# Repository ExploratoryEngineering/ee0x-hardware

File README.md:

# ee0x-hardware

* EE Eagle Library contains Eagle packages for ee0x modules and components used in the boards in this repository.
* EE02 v.1 Breakout is a breakout board for the initial version of EE02. This is an early version of the module that has a larger footprint than the production version.
* EE02 CO2 Sensor is an experimental gas sensor board for the initial version of EE02.

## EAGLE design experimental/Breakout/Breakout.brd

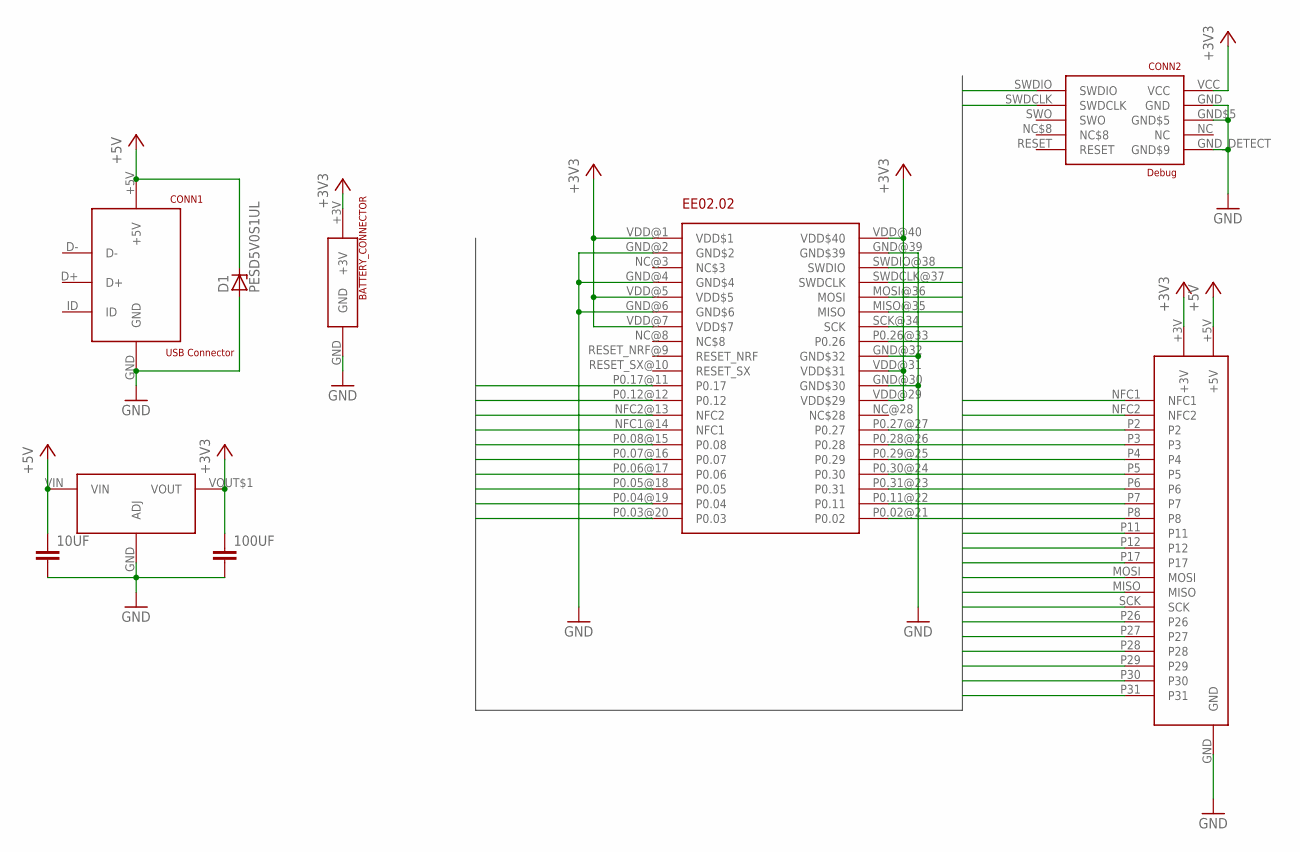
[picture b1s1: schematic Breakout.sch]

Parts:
10UF, 100UF: 4.7UF-0805; 0805
BATTERY_CONNECTOR: 3V_BATTERY_CONNECTOR
CONN1: USB Connector; USB_MICRO_B
CONN2: Debug; NRF52-P19-CONNECTOR
D1: PESD5V0S1UL; SOD882
EE02.02: EE02_02
U$4: LM1117; SOT-223
U$5: EE02_SHIELD_HEADERSHIELD; EE02_SHIELD_HEADER

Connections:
+3V3: 100UF.1, BATTERY_CONNECTOR.+3V, CONN2.VCC, EE02.02.VDD@1 (VDD$1), EE02.02.VDD@5 (VDD$5), EE02.02.VDD@7 (VDD$7), EE02.02.VDD@29 (VDD$29), EE02.02.VDD@31 (VDD$31), EE02.02.VDD@40 (VDD$40), U$4.VOUT$1 (VOUT), U$5.+3V
+5V: 10UF.1, CONN1.+5V, D1.CATHODE (C), U$4.VIN, U$5.+5V
GND: 10UF.2, 100UF.2, BATTERY_CONNECTOR.GND, CONN1.GND, CONN2.GND, CONN2.GND$5, CONN2.GND_DETECT (GND$9), D1.ANODE (A), EE02.02.GND@2 (GND$2), EE02.02.GND@4 (GND$4), EE02.02.GND@6 (GND$6), EE02.02.GND@30 (GND$30), EE02.02.GND@32 (GND$32), EE02.02.GND@39 (GND$39), U$4.GND (ADJ), U$5.GND
MISO: EE02.02.MISO@35 (MISO), U$5.MISO
MOSI: EE02.02.MOSI@36 (MOSI), U$5.MOSI
NFC1: EE02.02.NFC1@14 (NFC1), U$5.NFC1
NFC2: EE02.02.NFC2@13 (NFC2), U$5.NFC2
P2: EE02.02.P0.02@21 (P0.02), U$5.P2
P3: EE02.02.P0.03@20 (P0.03), U$5.P3
P4: EE02.02.P0.04@19 (P0.04), U$5.P4
P5: EE02.02.P0.05@18 (P0.05), U$5.P5
P6: EE02.02.P0.06@17 (P0.06), U$5.P6
P7: EE02.02.P0.07@16 (P0.07), U$5.P7
P8: EE02.02.P0.08@15 (P0.08), U$5.P8
P11: EE02.02.P0.11@22 (P0.11), U$5.P11
P12: EE02.02.P0.12@12 (P0.12), U$5.P12
P17: EE02.02.P0.17@11 (P0.17), U$5.P17
P26: EE02.02.P0.26@33 (P0.26), U$5.P26
P27: EE02.02.P0.27@27 (P0.27), U$5.P27
P28: EE02.02.P0.28@26 (P0.28), U$5.P28
P29: EE02.02.P0.29@25 (P0.29), U$5.P29
P30: EE02.02.P0.30@24 (P0.30), U$5.P30
P31: EE02.02.P0.31@23 (P0.31), U$5.P31
SCK: EE02.02.SCK@34 (SCK), U$5.SCK
SWDCLK: CONN2.SWDCLK, EE02.02.SWDCLK@37 (SWDCLK)
SWDIO: CONN2.SWDIO, EE02.02.SWDIO@38 (SWDIO)

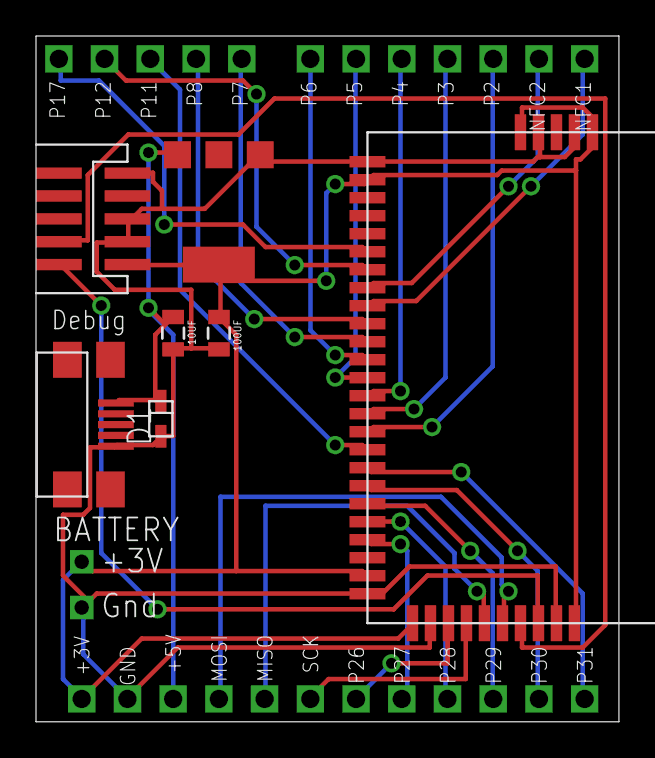
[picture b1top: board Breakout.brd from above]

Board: 2 copper layers, 32.4 x 38.1 mm, 9 parts (0 on the bottom side), 26 nets.

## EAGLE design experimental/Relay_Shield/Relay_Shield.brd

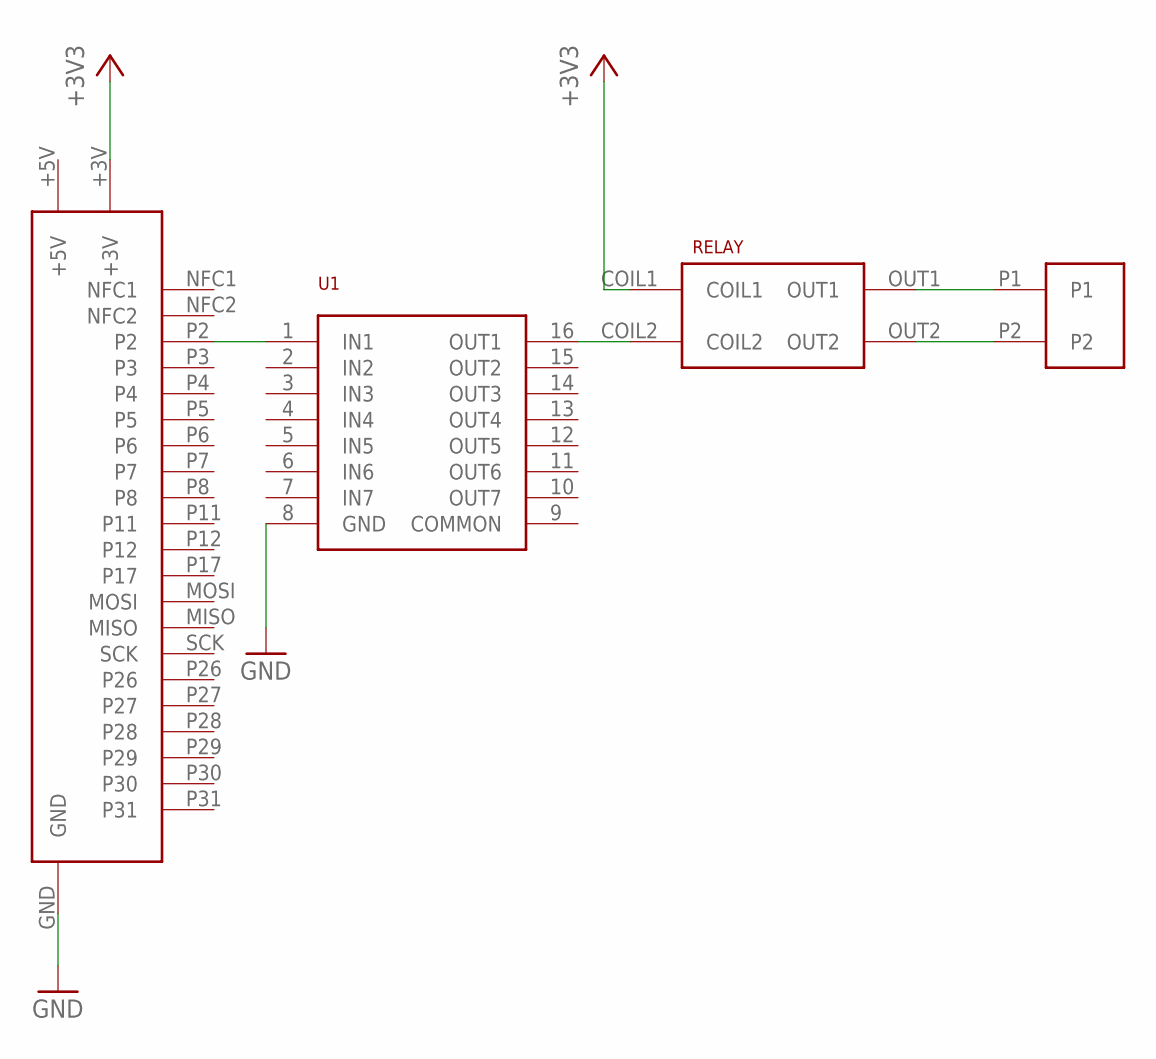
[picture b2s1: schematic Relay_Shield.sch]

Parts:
RELAY: 3V_RELAY_OZ-SS-103LM1
U1: ULN2003D1013TR; SO16-NARROW
U$1: EE02_SHIELD_HEADERSHIELD; EE02_SHIELD_HEADER
U$2: LOAD_TERMINAL_2P; LOAD_CONNECTOR_2P

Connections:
+3V3: RELAY.COIL1, U$1.+3V
GND: U1.8 (GND), U$1.GND
unnamed: U1.1 (IN1), U$1.P2
unnamed: RELAY.COIL2, U1.16 (OUT1)
unnamed: RELAY.OUT1, U$2.P1
unnamed: RELAY.OUT2, U$2.P2

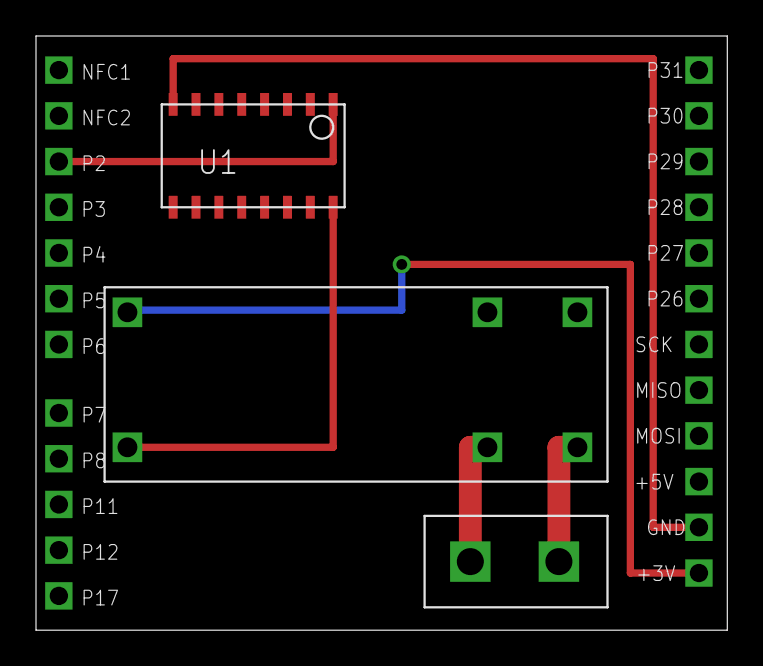
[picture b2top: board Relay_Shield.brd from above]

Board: 2 copper layers, 38.4 x 33.0 mm, 4 parts (0 on the bottom side), 6 nets.

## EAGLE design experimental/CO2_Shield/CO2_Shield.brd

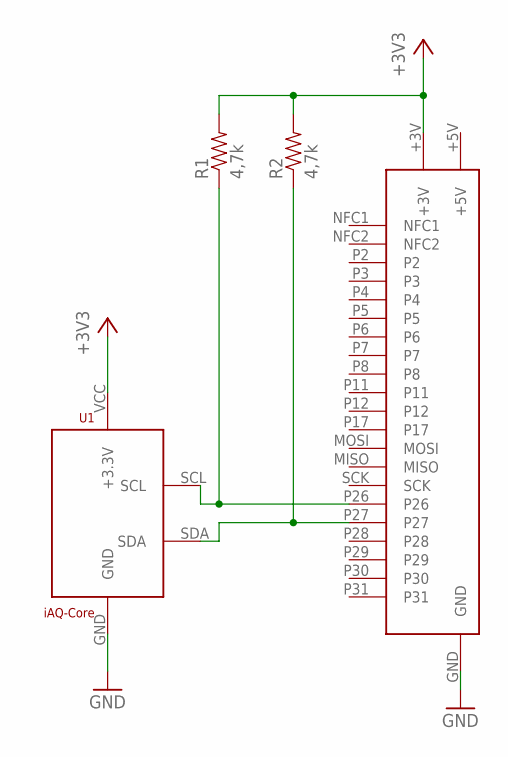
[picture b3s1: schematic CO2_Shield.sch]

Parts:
R1, R2: 4,7k; 0805
U1: iAQ-Core; IAQ-CORE
U$1: EE02_SHIELD_HEADERSHIELD; EE02_SHIELD_HEADER

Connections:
+3V3: R1.2, R2.2, U1.VCC (+3.3V), U$1.+3V
GND: U1.GND, U$1.GND
unnamed: R2.1, U1.SDA, U$1.P27
unnamed: R1.1, U1.SCL, U$1.P26

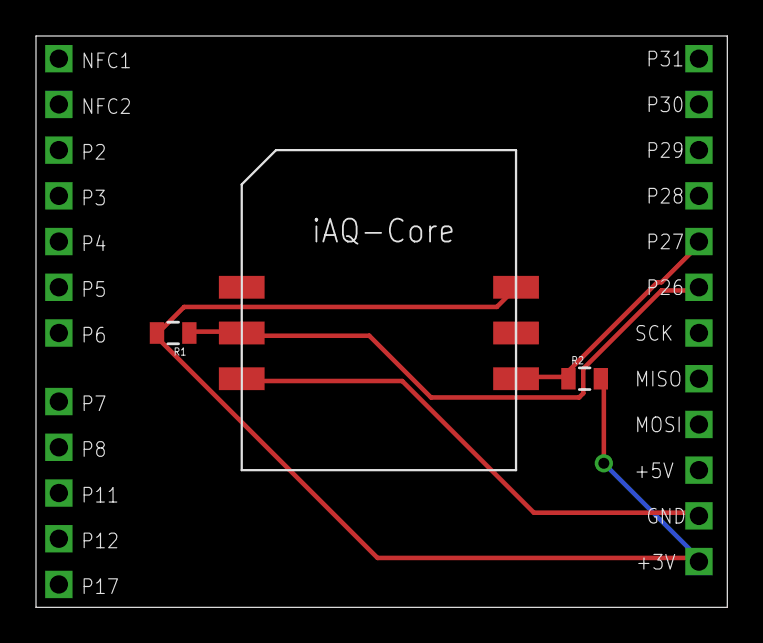
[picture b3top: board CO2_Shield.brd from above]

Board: 2 copper layers, 38.4 x 31.7 mm, 4 parts (0 on the bottom side), 4 nets.

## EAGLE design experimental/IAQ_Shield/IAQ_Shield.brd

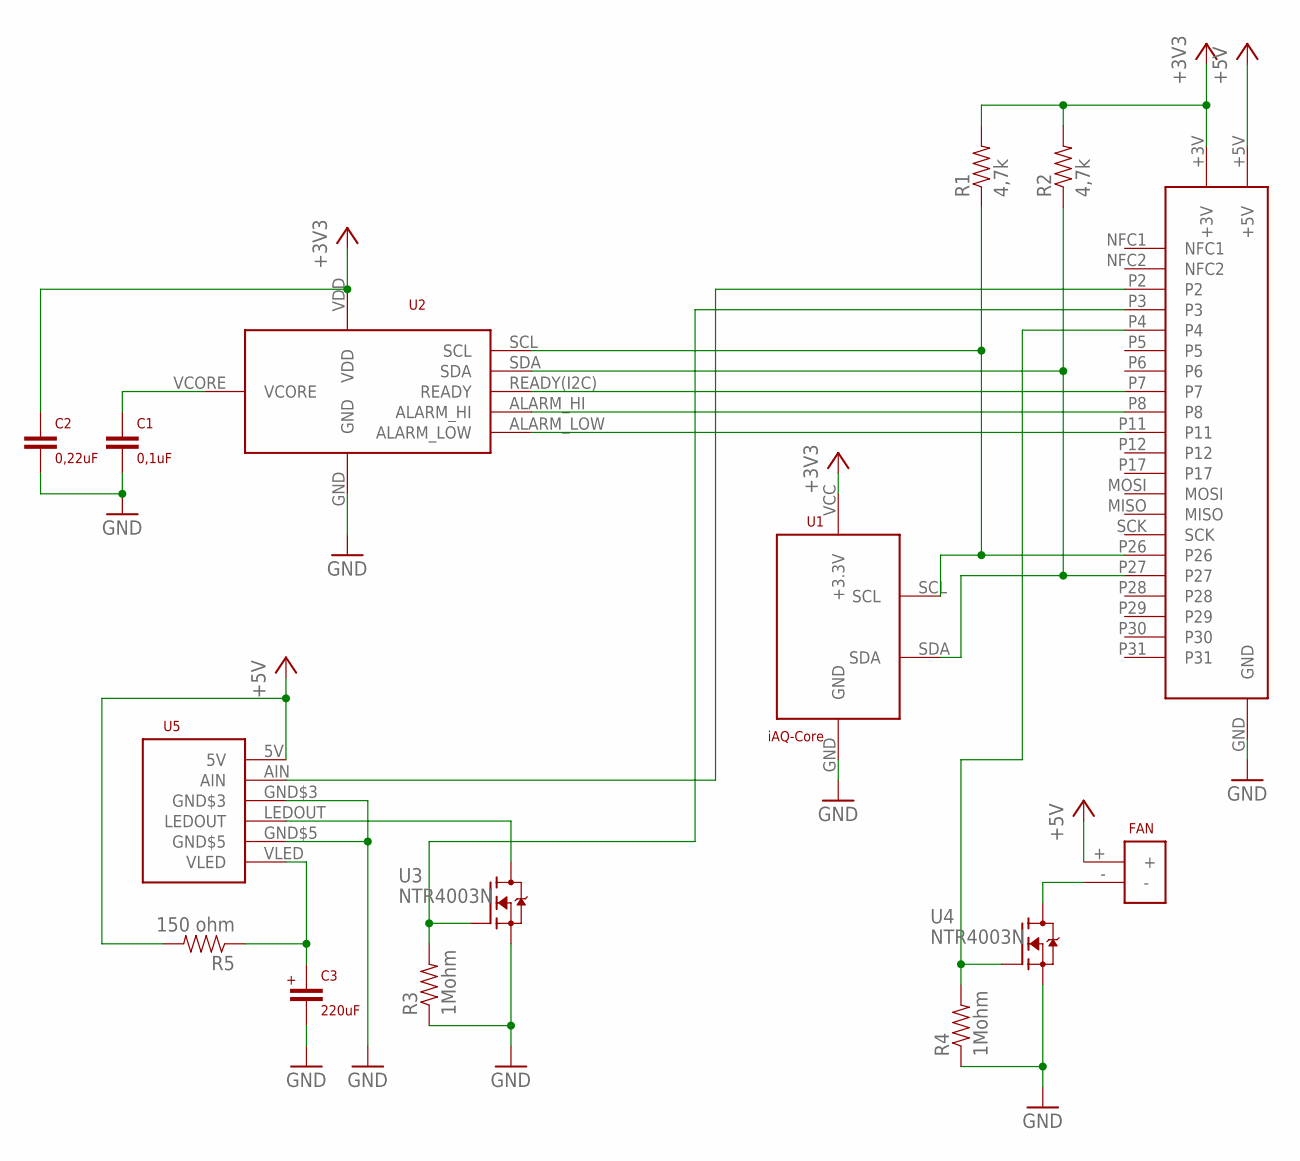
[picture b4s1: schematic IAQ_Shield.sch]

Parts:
C1: 0,1uF; 0805
C2: 0,22uF; 0805
C3: 220uF; UWT1C221MCL1GS_ALUMINIUM
FAN: POWER_SOLDER_PADS_2P
R1, R2: 4,7k; 0805
R3, R4: 1Mohm; 0805
R5: 150 ohm; 0805
U1: iAQ-Core; IAQ-CORE
U2: CHIPCAP2
U3, U4: NTR4003N; SOT23
U5: DN7C3CA006
U$1: EE02_SHIELD_HEADERSHIELD; EE02_SHIELD_HEADER

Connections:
+3V3: C2.1, R1.2, R2.2, U1.VCC (+3.3V), U2.VDD, U$1.+3V
+5V: FAN.+, R5.2, U5.5V, U$1.+5V
GND: C1.2, C2.2, C3.-, R3.1, R4.1, U1.GND, U2.GND, U3.2 (S), U4.2 (S), U5.GND$3, U5.GND$5, U$1.GND
unnamed: R2.1, U1.SDA, U2.SDA, U$1.P27
unnamed: R1.1, U1.SCL, U2.SCL, U$1.P26
unnamed: U5.AIN, U$1.P2
unnamed: U3.3 (D), U5.LEDOUT
unnamed: U2.READY(I2C) (READY), U$1.P7
unnamed: C1.1, U2.VCORE
unnamed: U2.ALARM_HI, U$1.P8
unnamed: U2.ALARM_LOW, U$1.P11
unnamed: R3.2, U3.1 (G), U$1.P3
unnamed: C3.+, R5.1, U5.VLED
unnamed: R4.2, U4.1 (G), U$1.P4
unnamed: FAN.-, U4.3 (D)

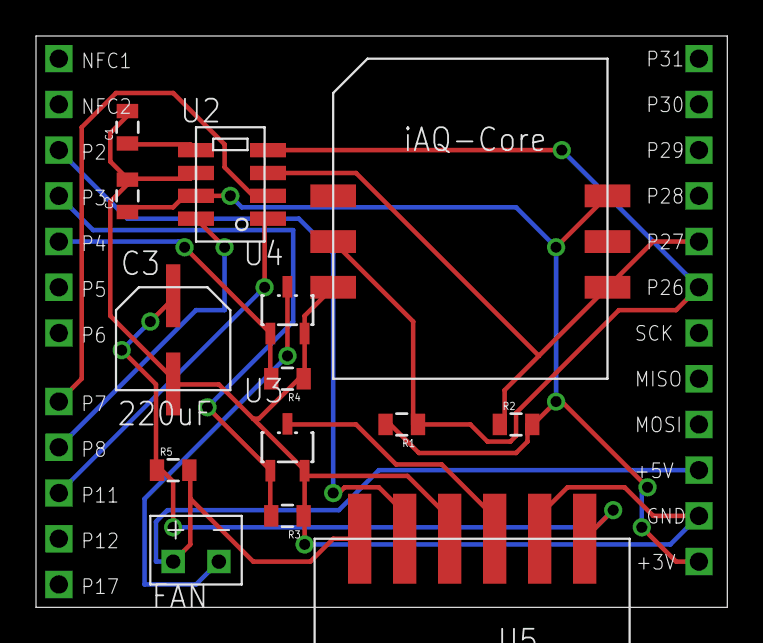
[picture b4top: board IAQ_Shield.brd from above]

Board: 2 copper layers, 38.4 x 31.7 mm, 15 parts (0 on the bottom side), 15 nets.

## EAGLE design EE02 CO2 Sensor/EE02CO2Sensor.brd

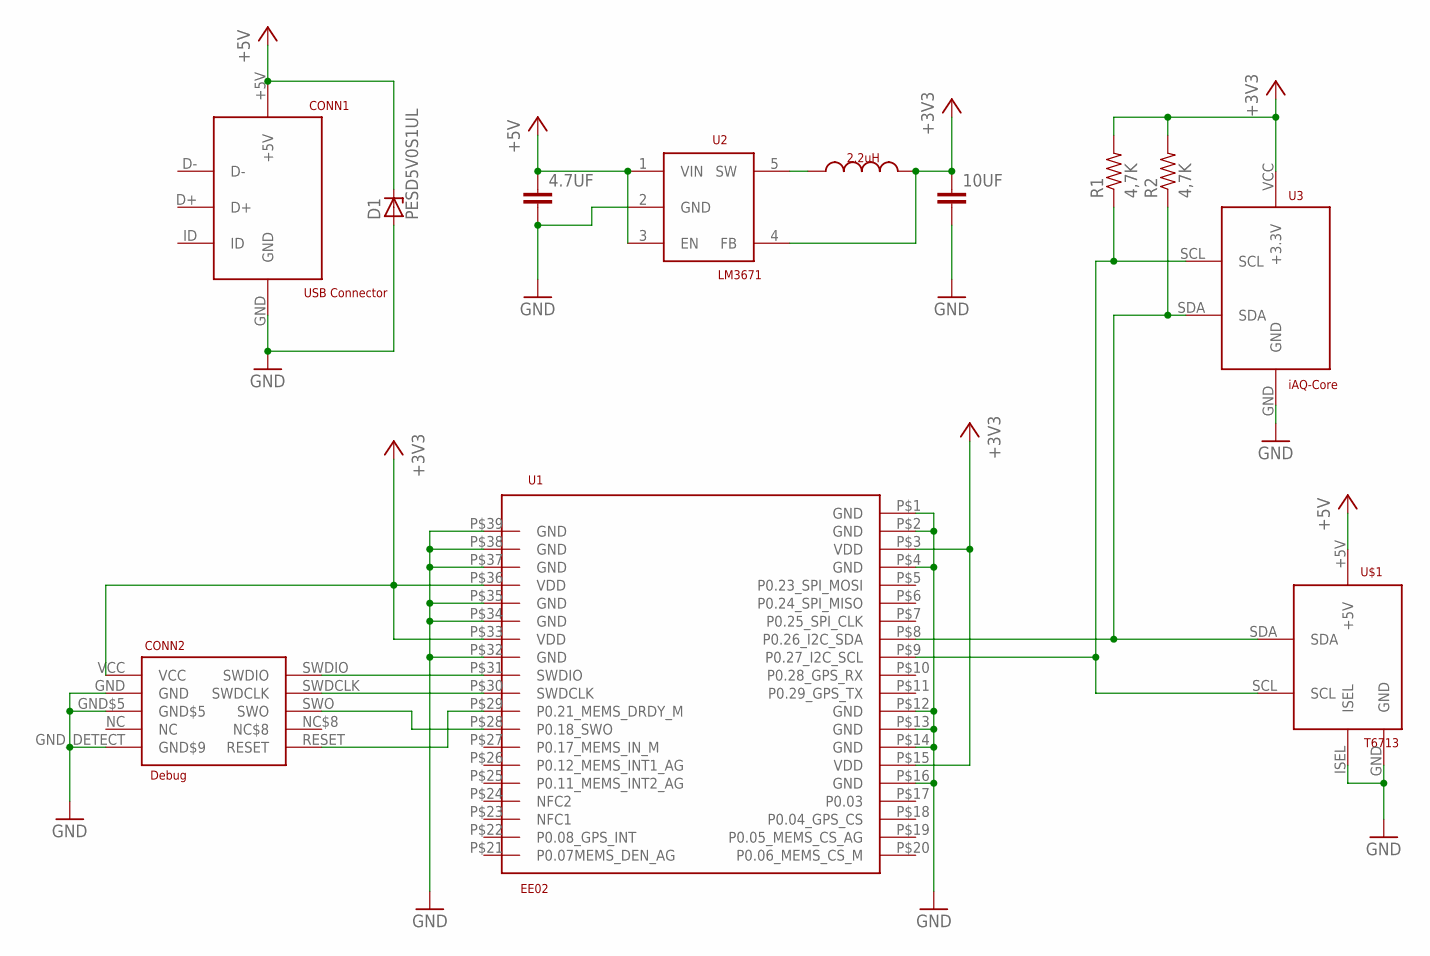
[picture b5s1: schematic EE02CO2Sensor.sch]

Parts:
4.7UF: 4.7UF-0805; 0805
10UF: 10UF-1206; 1206
CONN1: USB Connector; USB_MICRO_B
CONN2: Debug; NRF52-P19-CONNECTOR
D1: PESD5V0S1UL; SOD882
I1: 2.2uH; 1210
R1, R2: 4,7K; 0805
U1: EE02
U2: LM3671; SOT23-5L
U3: iAQ-Core; IAQ-CORE
U$1: T6713; T6713CO2

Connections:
+3V3: 10UF.1, CONN2.VCC, I1.2, R1.2, R2.2, U1.P$3 (VDD), U1.P$15 (VDD), U1.P$33 (VDD), U1.P$36 (VDD), U2.4 (FB), U3.VCC (+3.3V)
+5V: 4.7UF.1, CONN1.+5V, D1.CATHODE (C), U2.1 (VIN), U2.3 (EN), U$1.+5V
GND: 4.7UF.2, 10UF.2, CONN1.GND, CONN2.GND, CONN2.GND$5, CONN2.GND_DETECT (GND$9), D1.ANODE (A), U1.P$1 (GND), U1.P$2 (GND), U1.P$4 (GND), U1.P$12 (GND), U1.P$13 (GND), U1.P$14 (GND), U1.P$16 (GND), U1.P$32 (GND), U1.P$34 (GND), U1.P$35 (GND), U1.P$37 (GND), U1.P$38 (GND), U1.P$39 (GND), U2.2 (GND), U3.GND, U$1.GND, U$1.ISEL
unnamed: I1.1, U2.5 (SW)
unnamed: R2.1, U1.P$8 (P0.26_I2C_SDA), U3.SDA, U$1.SDA
unnamed: R1.1, U1.P$9 (P0.27_I2C_SCL), U3.SCL, U$1.SCL
unnamed: CONN2.SWDIO, U1.P$31 (SWDIO)
unnamed: CONN2.SWO, U1.P$28 (P0.18_SWO)
unnamed: CONN2.SWDCLK, U1.P$30 (SWDCLK)
unnamed: CONN2.RESET, U1.P$29 (P0.21_MEMS_DRDY_M)

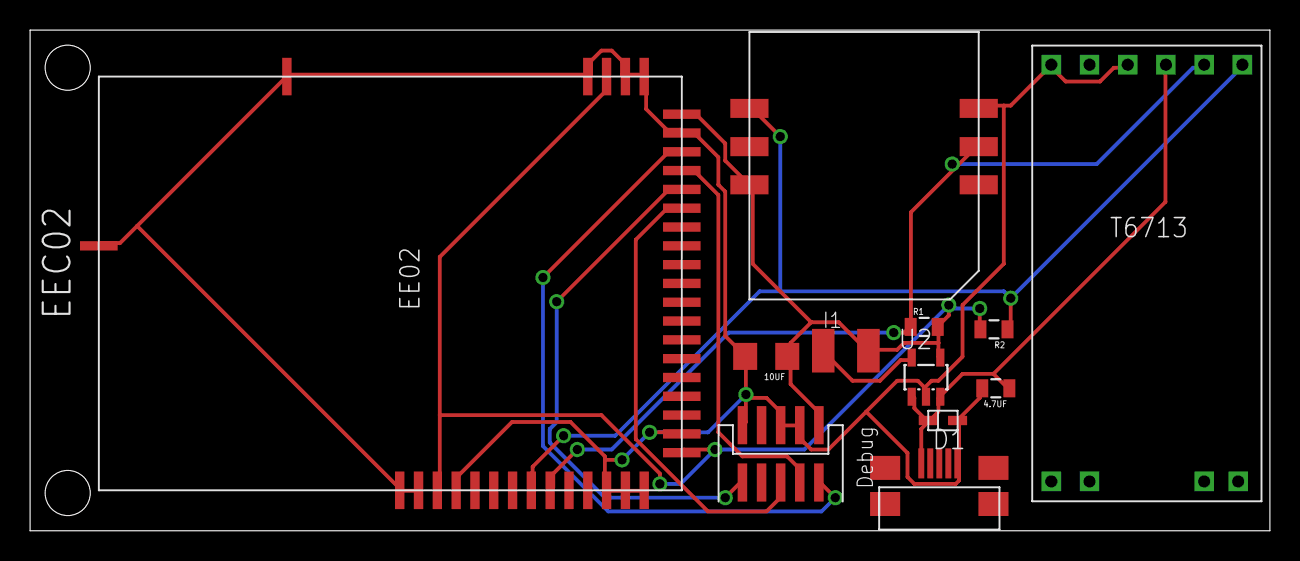
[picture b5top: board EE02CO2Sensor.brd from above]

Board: 2 copper layers, 82.4 x 33.3 mm, 12 parts (0 on the bottom side), 10 nets.

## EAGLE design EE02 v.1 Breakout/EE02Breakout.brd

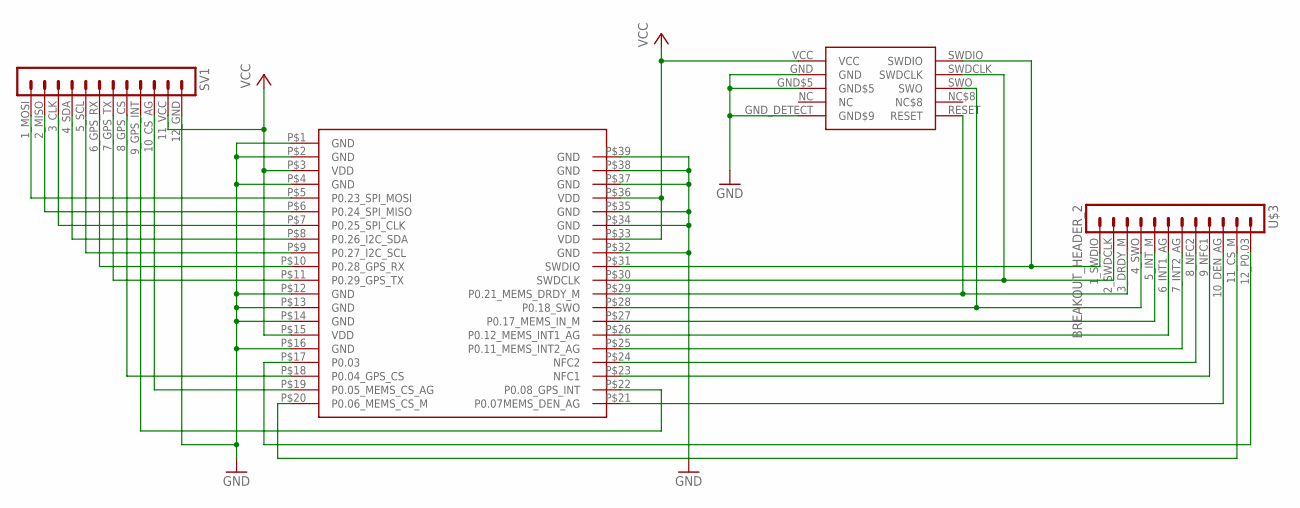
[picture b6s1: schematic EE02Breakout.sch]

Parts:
SV1: BREAKOUT_HEADER_1BREAKOUT_HEADER_2; BRH1
U$1: EE02
U$2: DEBUGHEADER; NRF52-P19-CONNECTOR
U$3: BREAKOUT_HEADER_2; BRH2

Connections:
GND: U$1.P$32 (GND), U$1.P$34 (GND), U$1.P$35 (GND), U$1.P$37 (GND), U$1.P$38 (GND), U$1.P$39 (GND), U$2.GND, U$2.GND$5, U$2.GND_DETECT (GND$9)
unnamed: SV1.12_GND, U$1.P$1 (GND), U$1.P$2 (GND), U$1.P$4 (GND), U$1.P$12 (GND), U$1.P$13 (GND), U$1.P$14 (GND), U$1.P$16 (GND)
unnamed: U$1.P$21 (P0.07MEMS_DEN_AG), U$3.10_DEN_AG
unnamed: U$1.P$20 (P0.06_MEMS_CS_M), U$3.11_CS_M
unnamed: SV1.10_CS_AG, U$1.P$19 (P0.05_MEMS_CS_AG)
unnamed: SV1.9_GPS_INT, U$1.P$22 (P0.08_GPS_INT)
unnamed: SV1.8_GPS_CS, U$1.P$18 (P0.04_GPS_CS)
unnamed: SV1.7_GPS_TX, U$1.P$11 (P0.29_GPS_TX)
unnamed: SV1.6_GPS_RX, U$1.P$10 (P0.28_GPS_RX)
unnamed: SV1.5_SCL, U$1.P$9 (P0.27_I2C_SCL)
unnamed: SV1.4_SDA, U$1.P$8 (P0.26_I2C_SDA)
unnamed: SV1.3_CLK, U$1.P$7 (P0.25_SPI_CLK)
unnamed: SV1.2_MISO, U$1.P$6 (P0.24_SPI_MISO)
unnamed: SV1.1_MOSI, U$1.P$5 (P0.23_SPI_MOSI)
unnamed: U$1.P$31 (SWDIO), U$2.SWDIO, U$3.1_SWDIO
unnamed: U$1.P$30 (SWDCLK), U$2.SWDCLK, U$3.2_SWDCLK
unnamed: U$1.P$29 (P0.21_MEMS_DRDY_M), U$2.RESET, U$3.3_DRDY_M
unnamed: U$1.P$28 (P0.18_SWO), U$2.SWO, U$3.4_SWO
unnamed: U$1.P$27 (P0.17_MEMS_IN_M), U$3.5_INT_M
unnamed: U$1.P$26 (P0.12_MEMS_INT1_AG), U$3.6_INT1_AG
unnamed: U$1.P$25 (P0.11_MEMS_INT2_AG), U$3.7_INT2_AG
unnamed: U$1.P$24 (NFC2), U$3.8_NFC2
unnamed: U$1.P$23 (NFC1), U$3.9_NFC1
unnamed: U$1.P$17 (P0.03), U$3.12_P0.03
VCC: SV1.11_VCC (11_3V), U$1.P$3 (VDD), U$1.P$15 (VDD), U$1.P$33 (VDD), U$1.P$36 (VDD), U$2.VCC

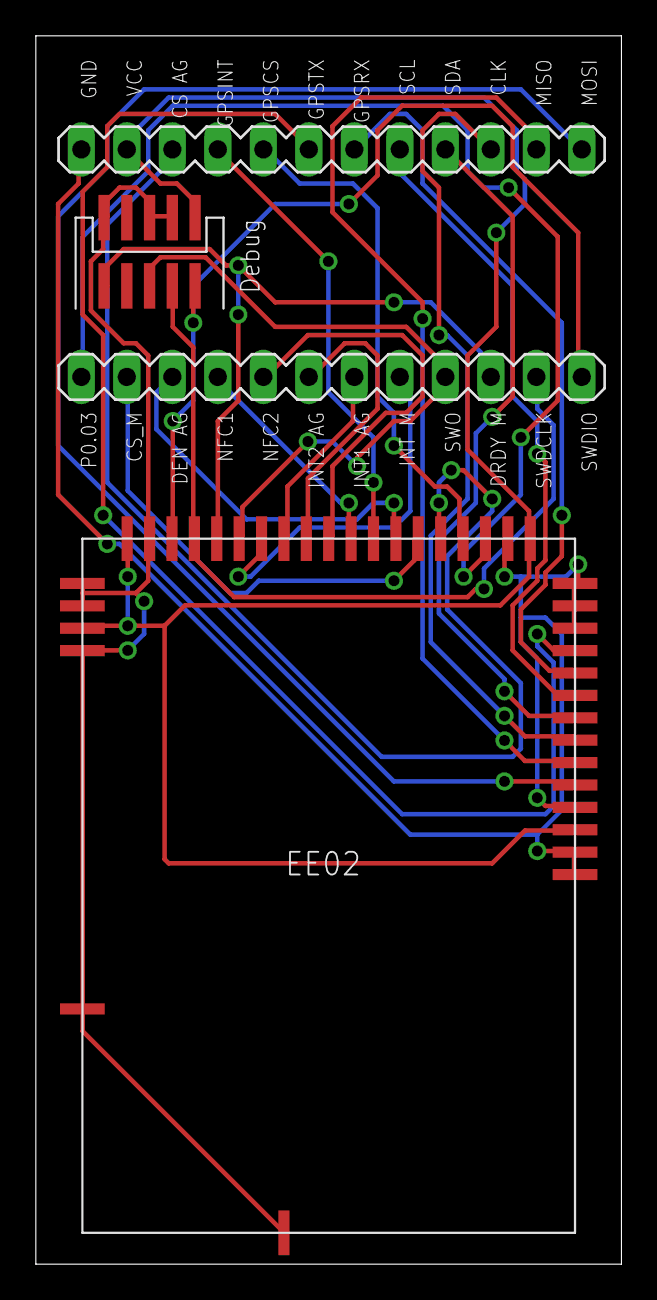
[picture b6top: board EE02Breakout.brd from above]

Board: 2 copper layers, 32.7 x 68.6 mm, 4 parts (0 on the bottom side), 25 nets.

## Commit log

2016-11-21 Initial version
2016-11-21 EE Eagle library + breakout board for EE02
2016-11-24 Added EE02 CO2 Sensor Board and schematics
    Updated EE library with new devices: iAQ-CORE, T6713, LM3671 and PCA9306
2016-11-24 CO2 Sensor board and schematics
    New devices in EE Library: iAQ-CORE, T6713, LM3671 and PCA9306
2016-12-16 Updated Co2 sensor board and schematics
    - Corrected footprint of micro USB Connector in library
    - Added interface select pin for 6713 device
    - Removed I2C level shifter (6713 can operate on 3.3V SDA/SCL)
    - Rotated EE02 180 degrees for optimal antenna placement
    - Added 4,7k pullups to SDA and SCL
    - Removed breakout brd/sch from sensor project
2017-01-24 EE-02 v2.1 - Altium Files
    Includes the tuned antenna network values based on the boards
    received from first prototype batch for this version.
2017-01-24 EE-02 v2.1 - Altium Files (#3)
    Includes the tuned antenna network values based on the boards
    received from first prototype batch for this version.
2017-03-06 Added package for EE02 2.1
2017-03-13 PDF with schematics
2017-03-13 Added prototype breakout and shields.
2017-03-24 Added model files for Gateway Scanner
2017-08-17 Center EE02 and iAQ core The mark you click to select them was not centered, like most other parts are. That makes it hard to find the mark to select/move/anything with the parts. Have corrected thos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
2017-08-25 Add momentary switch and footprint for Apem SMD tactile switch
